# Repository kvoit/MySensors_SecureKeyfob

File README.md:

# MySensors_SecureKeyfob
A keyfob for MySensors using the RFM69HCW and the ATSHA204 for authentication

Uses
* Sparkfun library for RFM69HCW
* MySensors library for ATSHA204

Fits into enclosure listed as
* CamdenBoss keyfob 2955-20R-5
* RND 455-00014 (in Germany e.g. from Reichelt)

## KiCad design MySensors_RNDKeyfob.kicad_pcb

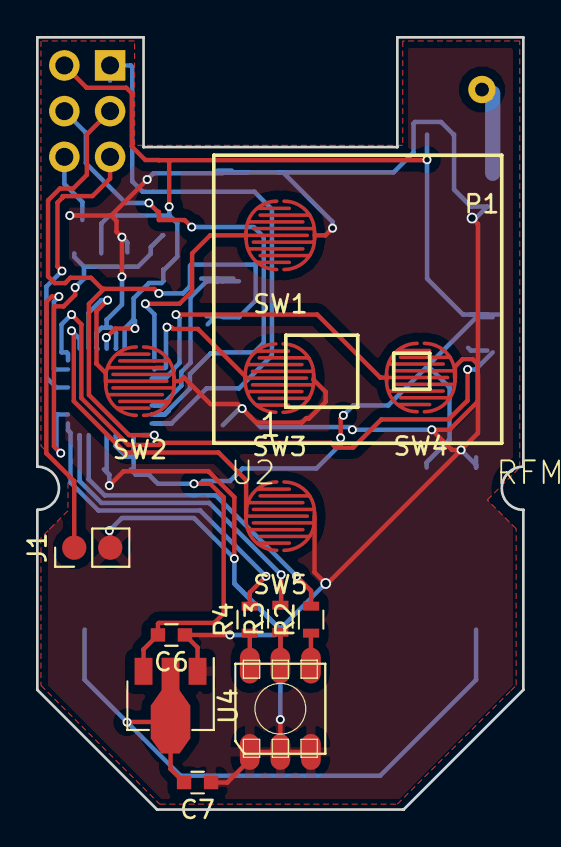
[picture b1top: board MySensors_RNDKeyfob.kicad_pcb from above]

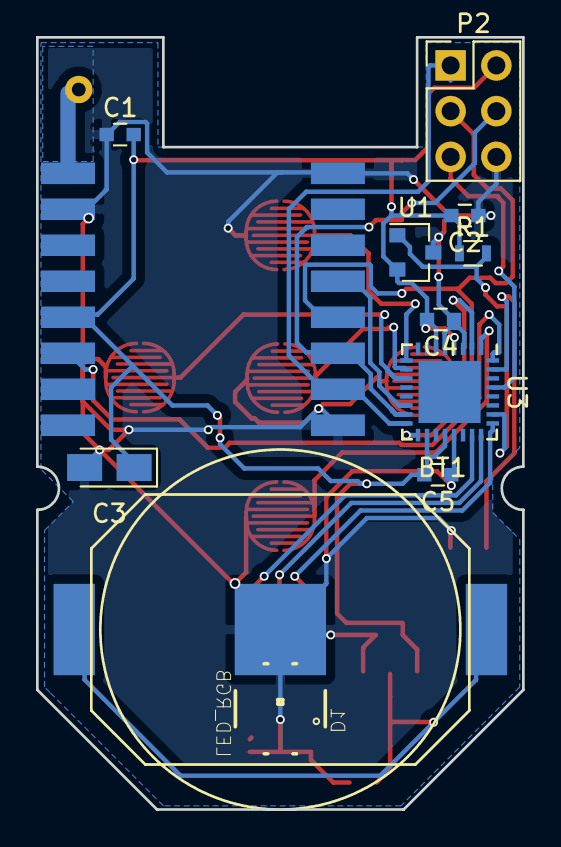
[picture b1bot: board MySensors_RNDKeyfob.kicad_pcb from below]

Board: 2 copper layers, 27.0 x 42.9 mm, 25 parts (11 on the bottom side), 23 nets.

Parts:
BT1: Battery; CR2032Holder
C1, C2, C4, C5: 100n; C_0603
C3: CP; CP_Tantalum_Case-A_EIA-3216-18_Reflow
C6, C7: C; C_0603
D1: LED_RGB; LED-TRICOLOR-5050
J1: CONN_01X02; Pin_Header_Straight_1x02_Pitch2.00mm
P1: CONN_01X01; 868MHz_Spring_Antenna
P2: CONN_02X03; Pin_Header_Straight_2x03_Pitch2.54mm
R1: 1K; R_0603
R2, R3, R4: R; R_0603
SW1, SW2, SW3, SW4, SW5: SW_SPST; 4mm_Rubber_Button
U1: ATSHA204A; SOT-23
U2: RFM69HCW; RFM69HCW-XXXS2
U3: ATMEGA328P-MU; QFN-32-1EP_5x5mm_Pitch0.5mm
U4: HT7333; SOT-89-3

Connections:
/A0: R2.2, U3.23
/A1: R3.2, U3.24
/A2: R4.2, U3.25
/A3: R1.2, U1.1, U3.26
/ANT: P1.1, U2.9
/D2: U2.14, U3.32
/D3: SW5.1, U3.1
/D4: SW2.1, U3.2
/D5: SW1.1, U3.9
/D6: SW3.1, U3.10
/D7: SW4.1, U3.11
/D10: U2.5, U3.14
/MISO: P2.1, U2.2, U3.16
/MOSI: P2.4, U2.3, U3.15
/RESET: P2.5, U3.29
/SCK: P2.3, U2.4, U3.17
/TXO: J1.1, U3.31
/VCC: C1.2, C2.2, C3.1, C4.2, C5.2, C6.2, P2.2, R1.1, U1.2, U2.13, U3.4, U3.6, U3.18, U3.20, U4.3
GND: BT1.2, C1.1, C2.1, C3.2, C4.1, C5.1, C6.1, C7.1, D1.1, D1.2, D1.3, J1.2, P2.6, SW1.2, SW2.2, SW3.2, SW4.2, SW5.2, U1.3, U2.1, U2.8, U2.10, U3.3, U3.5, U3.21, U4.1
unnamed: BT1.1, C7.2, U4.2
unnamed: D1.4, R2.1
unnamed: D1.5, R3.1
unnamed: D1.6, R4.1

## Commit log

2017-04-19 Added library infor to README
2017-04-19 Added info about enclosure
2017-04-22 Turned ICSP header to backside, improved rubber button pads
2017-04-22 Added RGB LED
2017-04-25 Changed antenna net impedance to 50 Ohm
2017-04-29 Fine tuning with antenna, trace distances to v-cuts, position of RGB LED
2017-04-29 Tiled with v-cut for production, added Gerbers
2017-05-28 Added HT7333 to allow for LIR2032 lithium coin cell (Bridge pads for CR2032). Changed A7 to A2 to make LED work. Added SMD contacts for TX and GND for debug output (interface with pogo pins).
2017-05-28 Doubled size of battery pads. Added HT7333 to allow for LIR2032 lithium coin cell (Bridge pads for CR2032). Changed A7 to A2 to make LED work. Added SMD contacts for TX and GND for debug output (inte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
2017-05-28 Added pull-up to CS line to stablize ICSP programming
